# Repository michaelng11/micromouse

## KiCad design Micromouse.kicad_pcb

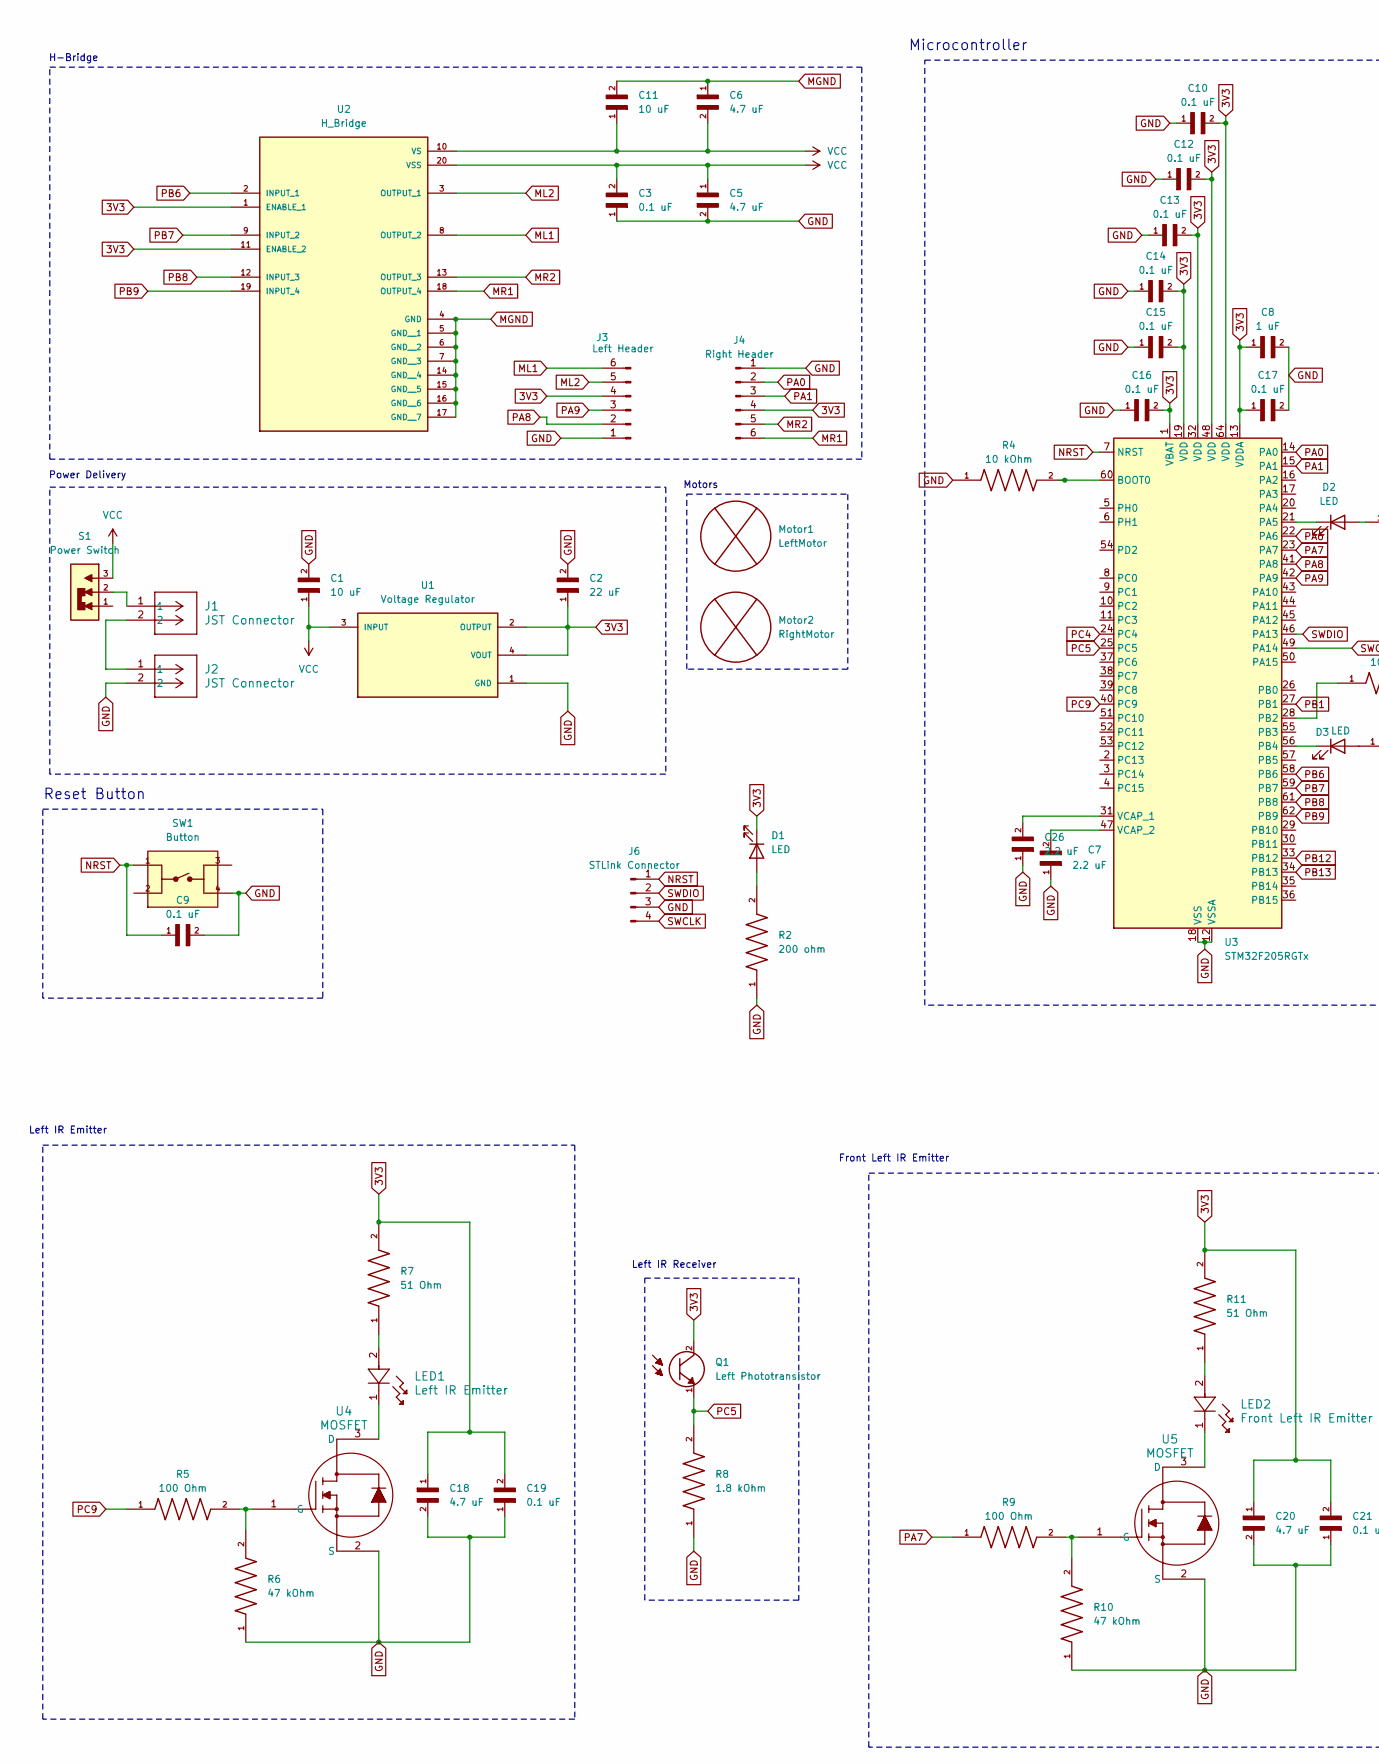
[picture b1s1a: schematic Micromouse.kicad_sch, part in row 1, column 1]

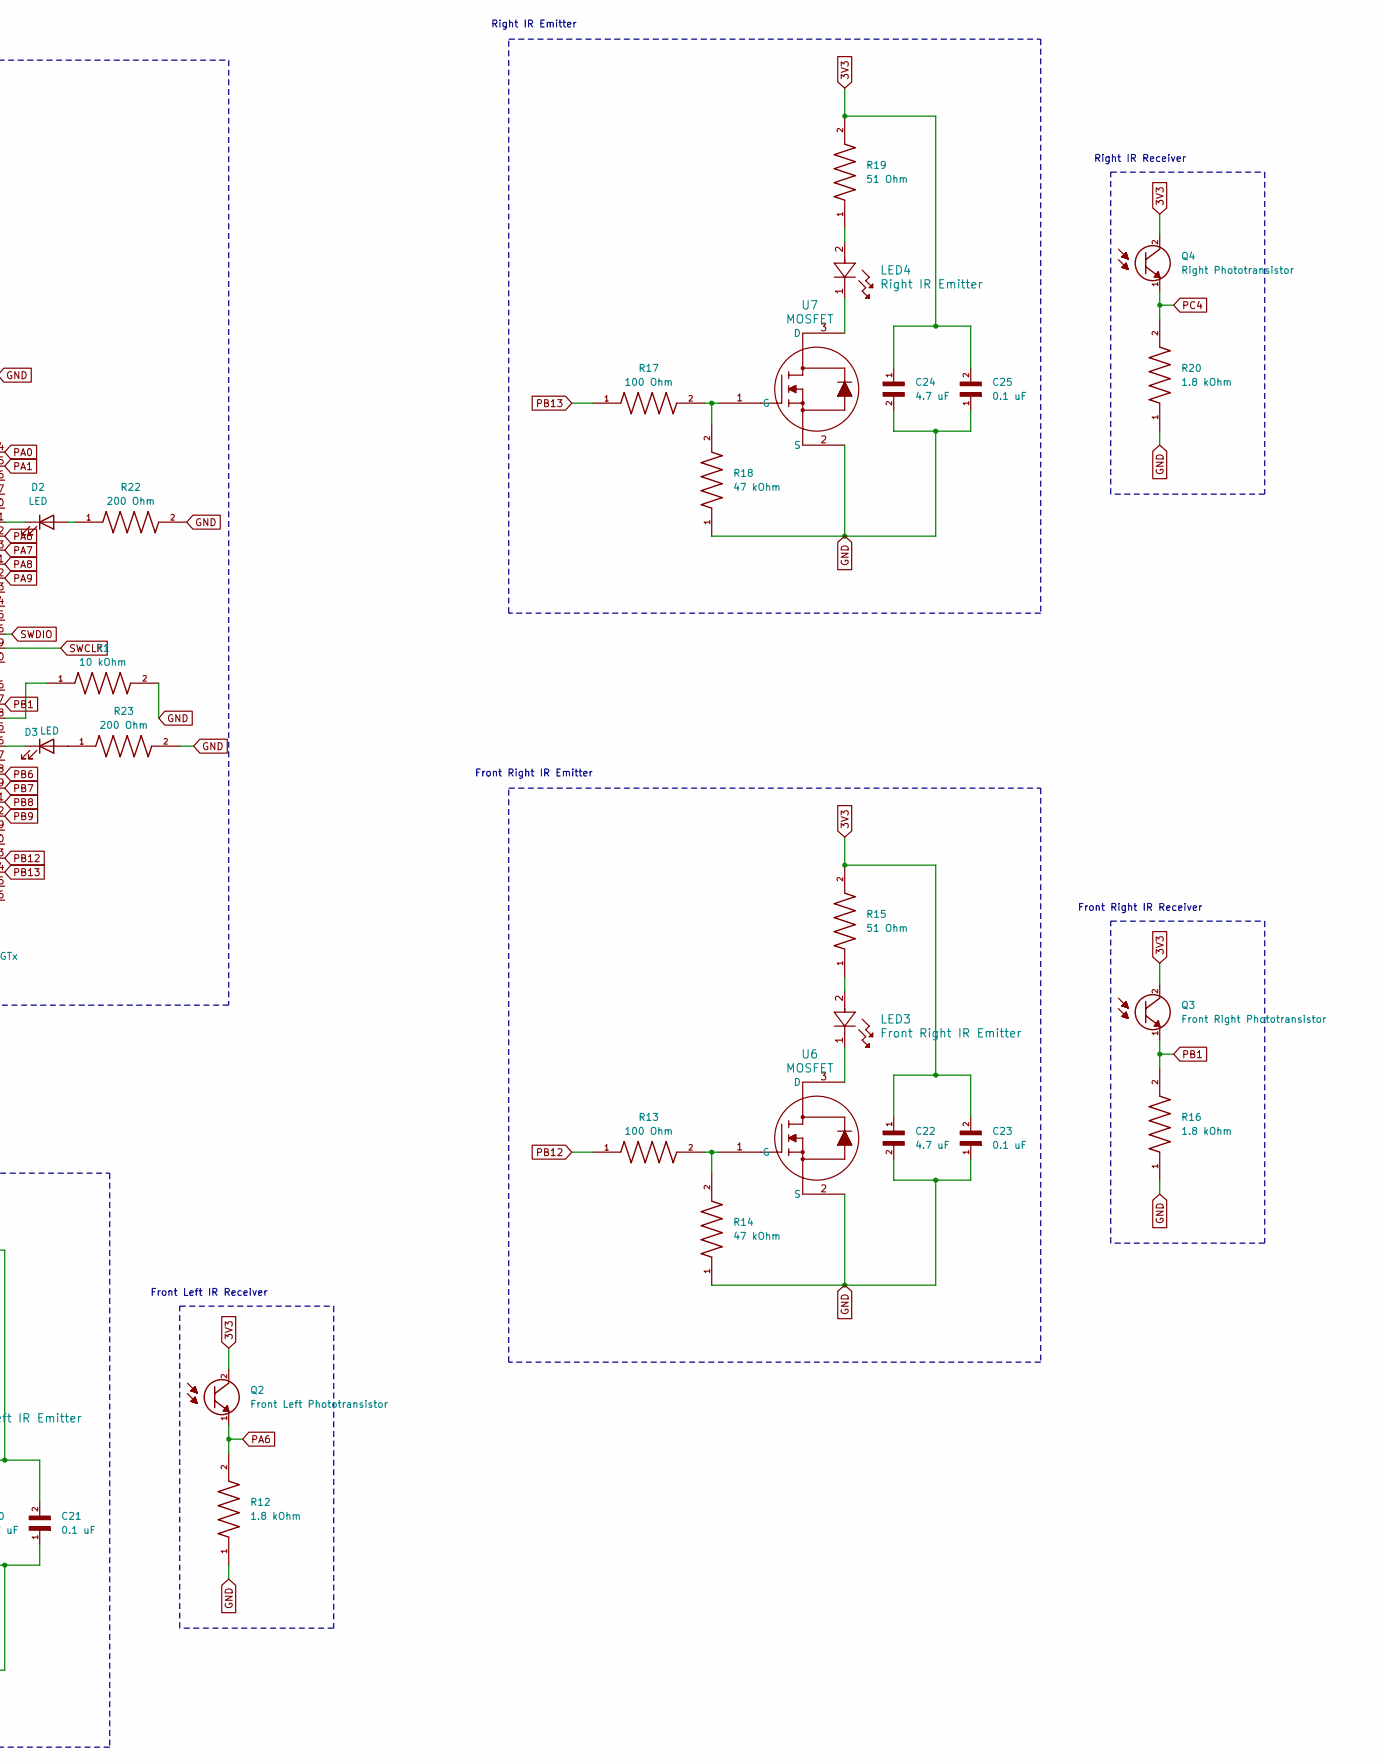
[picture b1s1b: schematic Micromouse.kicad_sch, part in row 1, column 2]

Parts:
C1, C11: 10 uF; CAPC2012X140N
C2: 22 uF; CAPC2012X140N
C3, C9, C10, C12, C13, C14, C15, C16, C17, C19, C21, C23, C25: 0.1 uF; CAPC2012X95N
C5, C6, C18, C20, C22, C24: 4.7 uF; CAPC2012X140N
C7, C26: 2.2 uF; CAPC2012X145N; DigiKey_Part_Number 445-5968-1-ND
C8: 1 uF; CAPC2012X135N; DigiKey_Part_Number 1276-1029-1-ND
D1, D2, D3: LED; LTST-C170GKT
J1, J2: JST Connector; CONN2_B2B-PH-K-S_JST
J3: Left Header; PinHeader_1x06_P1.27mm_Vertical
J4: Right Header; PinHeader_1x06_P1.27mm_Vertical
J6: STLink Connector; PinSocket_1x04_P2.54mm_Vertical
LED1: Left IR Emitter; LED_INL-5AMIR15_INO
LED2: Front Left IR Emitter; LED_INL-5AMIR15_INO
LED3: Front Right IR Emitter; LED_INL-5AMIR15_INO
LED4: Right IR Emitter; LED_INL-5AMIR15_INO
Motor1: LeftMotor; Pololu_Motor
Motor2: RightMotor; Pololu_Motor
Q1: Left Phototransistor; XDCR_SFH_313_FA-3_4; PARTREV 1.3; DigiKey_Part_Number 475-SFH313FA-3/4-ND
Q2: Front Left Phototransistor; XDCR_SFH_313_FA-3_4; PARTREV 1.3; DigiKey_Part_Number 475-SFH313FA-3/4-ND
Q3: Front Right Phototransistor; XDCR_SFH_313_FA-3_4; PARTREV 1.3; DigiKey_Part_Number 475-SFH313FA-3/4-ND
Q4: Right Phototransistor; XDCR_SFH_313_FA-3_4; PARTREV 1.3; DigiKey_Part_Number 475-SFH313FA-3/4-ND
R1, R4: 10 kOhm; RESC2012X60N; DigiKey_Part_Number 311-10KARCT-ND
R2: 200 ohm; RES_ERJP06F2000V; PARTREV 3/1/2020; DigiKey_Part_Number P16064CT-ND
R5, R9, R13, R17: 100 Ohm; RESC2012X60N; DigiKey_Part_Number 311-100CRCT-ND
R6, R10, R14, R18: 47 kOhm; RESC2012X60N; DigiKey_Part_Number 311-47.0KCRCT-ND
R7, R11, R15, R19: 51 Ohm; RESC2012X60N; DigiKey_Part_Number 311-51.0CRCT-ND
R8, R12, R16, R20: 1.8 kOhm; RESC2012X60N; DigiKey_Part_Number 311-1.80KCRCT-ND
R22, R23: 200 Ohm; RES_ERJP06F2000V; PARTREV 3/1/2020; DigiKey_Part_Number P16064CT-ND
S1: Power Switch; SW_EG1218; DigiKey_Part_Number EG1903-ND
SW1: Button; TE_FSM4JSMA; PARTREV V
U1: Voltage Regulator; SOT230P700X185-4N; PARTREV 2-2
U2: H_Bridge; SOIC127P1032X265-20N; PARTREV N/A
U3: STM32F205RGTx; LQFP-64_10x10mm_P0.5mm
U4, U5, U6, U7: MOSFET; SOT-23_ONS

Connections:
3V3: C2.1, C8.1, C10.2, C12.2, C13.2, C14.2, C15.2, C16.2, C17.1, C18.1, C19.2, C20.1, C21.2, C22.1, C23.2, C24.1, C25.2, D1.1 (K), J3.4, J4.4, Q1.2, Q2.2, Q3.2, Q4.2, R7.2, R11.2, R15.2, R19.2, U1.2 (OUTPUT), U1.4 (VOUT), U2.1 (ENABLE_1), U2.11 (ENABLE_2), U3.1 (VBAT), U3.13 (VDDA), U3.19 (VDD), U3.32 (VDD), U3.48 (VDD), U3.64 (VDD)
GND: C1.2, C2.2, C3.1, C5.2, C7.1, C8.2, C9.2, C10.1, C12.1, C13.1, C14.1, C15.1, C16.1, C17.2, C18.2, C19.1, C20.2, C21.1, C22.2, C23.1, C24.2, C25.1, C26.1, J2.2, J3.1, J4.1, J6.3, R1.2, R2.1, R4.1, R6.1, R8.1, R10.1, R12.1, R14.1, R16.1, R18.1, R20.1, R22.2, R23.2, SW1.4, U1.1 (GND), U3.12 (VSSA), U3.18 (VSS), U3.63 (VSS), U4.2 (S), U5.2 (S), U6.2 (S), U7.2 (S)
MGND: C6.1, C11.2, U2.4 (GND), U2.5 (GND__1), U2.6 (GND__2), U2.7 (GND__3), U2.14 (GND__4), U2.15 (GND__5), U2.16 (GND__6), U2.17 (GND__7)
ML1: J3.6, U2.8 (OUTPUT_2)
ML2: J3.5, U2.3 (OUTPUT_1)
MR1: J4.6, U2.18 (OUTPUT_4)
MR2: J4.5, U2.13 (OUTPUT_3)
NRST: C9.1, J6.1, SW1.1, U3.7 (NRST)
unnamed: D1.2 (A), R2.2
unnamed: D2.2 (A), R22.1
unnamed: D2.1 (K), U3.21 (PA5)
unnamed: D3.2 (A), R23.1
unnamed: D3.1 (K), U3.56 (PB4)
unnamed: J1.1, S1.2
unnamed: J1.2, J2.1
unnamed: LED1.2, R7.1
unnamed: LED2.2, R11.1
unnamed: LED3.2, R15.1
unnamed: LED4.2, R19.1
unnamed: R4.2, U3.60 (BOOT0)
unnamed: R1.1, U3.28 (PB2)
unnamed: C26.2, U3.31 (VCAP_1)
unnamed: C7.2, U3.47 (VCAP_2)
unnamed: LED1.1, U4.3 (D)
unnamed: R5.2, R6.2, U4.1 (G)
unnamed: LED2.1, U5.3 (D)
unnamed: R9.2, R10.2, U5.1 (G)
unnamed: LED3.1, U6.3 (D)
unnamed: R13.2, R14.2, U6.1 (G)
unnamed: LED4.1, U7.3 (D)
unnamed: R17.2, R18.2, U7.1 (G)
PA0: J4.2, U3.14 (PA0)
PA1: J4.3, U3.15 (PA1)
PA6: Q2.1, R12.2, U3.22 (PA6)
PA7: R9.1, U3.23 (PA7)
PA8: J3.2, U3.41 (PA8)
PA9: J3.3, U3.42 (PA9)
PB1: Q3.1, R16.2, U3.27 (PB1)
PB6: U2.2 (INPUT_1), U3.58 (PB6)
PB7: U2.9 (INPUT_2), U3.59 (PB7)
PB8: U2.12 (INPUT_3), U3.61 (PB8)
PB9: U2.19 (INPUT_4), U3.62 (PB9)
PB12: R13.1, U3.33 (PB12)
PB13: R17.1, U3.34 (PB13)
PC4: Q4.1, R20.2, U3.24 (PC4)
PC5: Q1.1, R8.2, U3.25 (PC5)
PC9: R5.1, U3.40 (PC9)
SWCLK: J6.4, U3.49 (PA14)
SWDIO: J6.2, U3.46 (PA13)
VCC: C1.1, C3.2, C5.1, C6.2, C11.1, S1.3, U1.3 (INPUT), U2.10 (VS), U2.20 (VSS)

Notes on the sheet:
Left IR Receiver
Right IR Emitter
Front Right IR Receiver
Left IR Emitter
Front Right IR Emitter
Right IR Receiver
Front Left IR Emitter
Motors
H-Bridge
Power Delivery
Microcontroller
Front Left IR Receiver
Reset Button

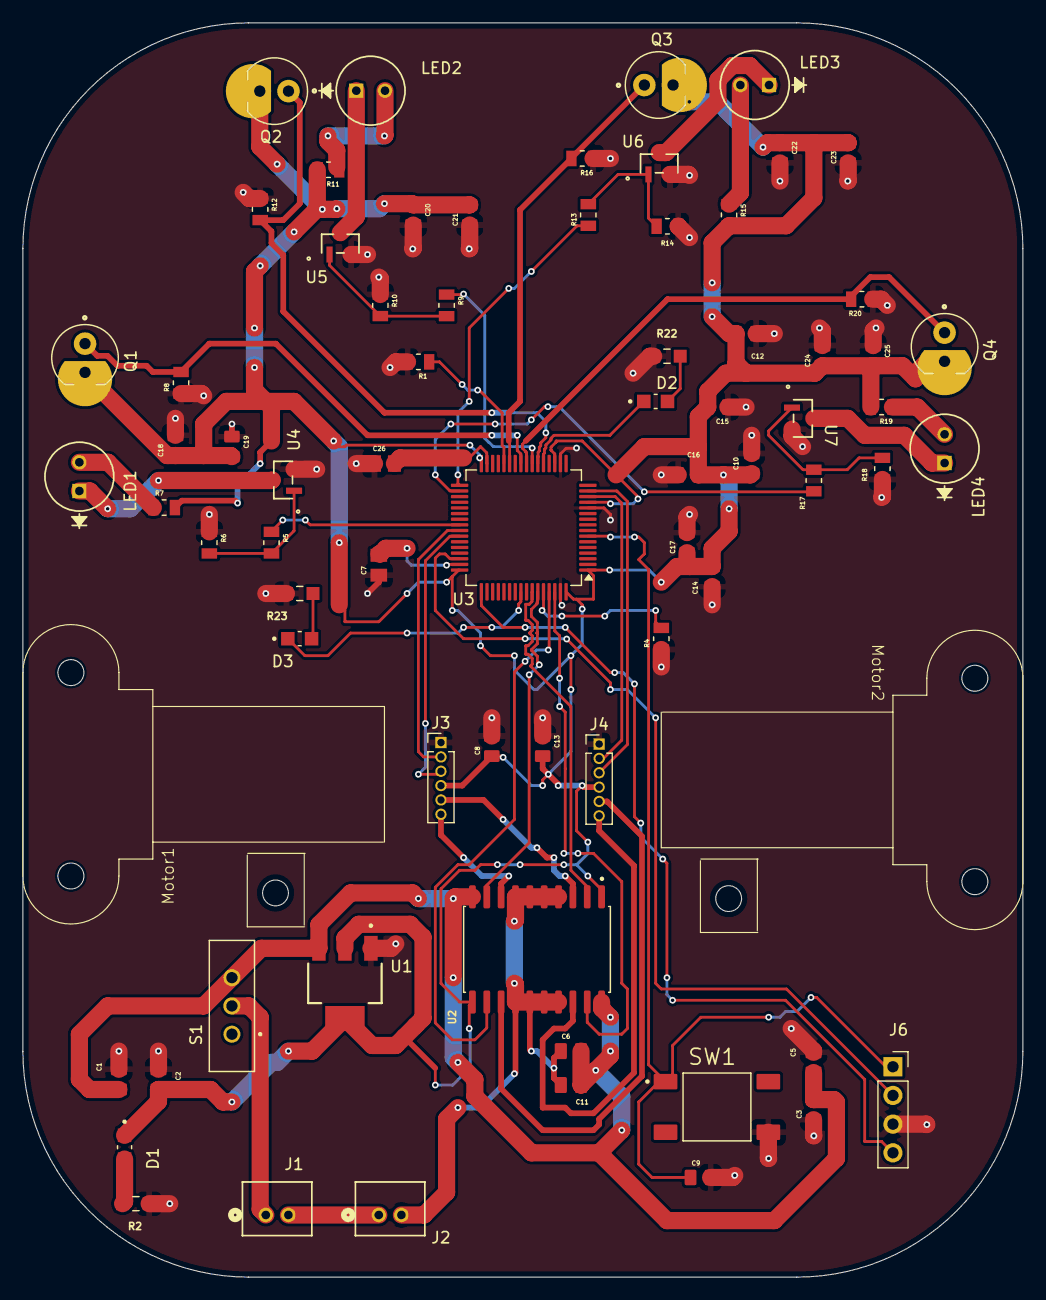
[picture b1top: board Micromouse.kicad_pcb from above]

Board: 2 copper layers, 88.5 x 111.0 mm, 73 parts (0 on the bottom side), 50 nets.

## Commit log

2026-03-06 added project specific symbols and footprints
2026-03-07 added power delivery to pcb
2026-03-07 fixed errors
2026-03-07 Cleanup
2026-03-07 updated power delivery
2026-03-08 Reorganized components
2026-03-08 ir
    renamed ir emitters and reformatted the pcb a little bit
2026-03-08 rough draft for routing
2026-03-08 finished pcb and fixed schematic
2026-03-09 added 2nd battery holder + front GND plane
2026-03-09 removed vias to bottom GND plane
2026-03-09 Revert "removed vias to bottom GND plane"
    This reverts commit 8af362b02ed4e9e0bd4abfa65a92dd62bbb7adce.
2026-03-09 Add stiching vias to front GND plane
2026-03-09 Revert to 4fd8e70
2026-03-09 fixed issues kevin pointed out
    compacted the pcb, fixed nrst misspelling, re-added two copper planes
2026-03-09 reattached nrst
